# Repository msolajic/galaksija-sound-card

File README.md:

# galaksija-sound-card
"Sound card" for Galaksija computer

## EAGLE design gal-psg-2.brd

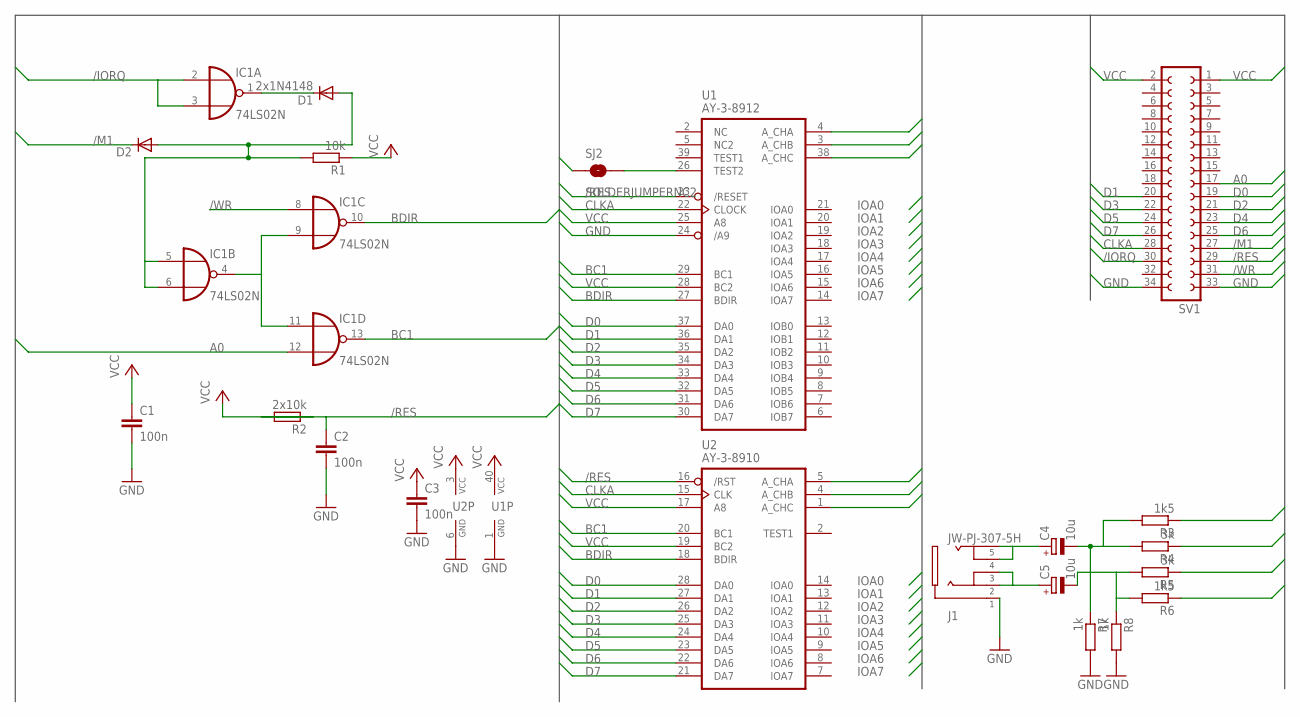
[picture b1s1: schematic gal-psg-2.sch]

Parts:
C1, C2, C3: 100n; C025-024X044
C4, C5: 10u; E1,8-4
D1: 2x1N4148; D-2.5
D2: DIODE-D-2.5; D-2.5
IC1: 74LS02N; DIL14
J1: JW-PJ-307-5H
R1: 10k; 0207/2V
R2: 2x10k; 0207/2V
R3, R6: 1k5; 0207/2V
R4, R5: 3k; 0207/2V
R7, R8: 1k; 0207/2V
SJ2: SOLDERJUMPERNC2; SJ_2S-NOTRACE
SV1: FE17-2W
U1: AY-3-8912; DIL40
U2: AY-3-8910; DIL28-6

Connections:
/IORQ: IC1.2 (I0), IC1.3 (I1), SV1.30
/M1: D2.C, SV1.27
/RES: C2.1, R2.2, SV1.29, U1.23 (/RESET), U2.16 (/RST)
/WR: IC1.8 (I0), SV1.31
A: R3.1, U1.4 (A_CHA), U2.5 (A_CHA)
A0: IC1.12 (I1), SV1.17
B: R4.1, R5.1, U1.3 (A_CHB), U2.4 (A_CHB)
BC1: IC1.13 (O), U1.29 (BC1), U2.20 (BC1)
BDIR: IC1.10 (O), U1.27 (BDIR), U2.18 (BDIR)
C: R6.1, U1.38 (A_CHC), U2.1 (A_CHC)
CLKA: SV1.28, U1.22 (CLOCK), U2.15 (CLK)
D0: SV1.19, U1.37 (DA0), U2.28 (DA0)
D1: SV1.20, U1.36 (DA1), U2.27 (DA1)
D2: SV1.21, U1.35 (DA2), U2.26 (DA2)
D3: SV1.22, U1.34 (DA3), U2.25 (DA3)
D4: SV1.23, U1.33 (DA4), U2.24 (DA4)
D5: SV1.24, U1.32 (DA5), U2.23 (DA5)
D6: SV1.25, U1.31 (DA6), U2.22 (DA6)
D7: SV1.26, U1.30 (DA7), U2.21 (DA7)
GND: C1.2, C2.2, C3.2, IC1.7 (GND), J1.1, R7.2, R8.2, SJ2.1, SV1.33, SV1.34, U1.1 (GND), U1.24 (/A9), U2.6 (GND)
unnamed: SJ2.2, U1.26 (TEST2)
unnamed: D1.C, IC1.1 (O)
unnamed: C5.+, J1.2, J1.3
unnamed: D1.A, D2.A, IC1.5 (I0), IC1.6 (I1), R1.2
unnamed: C4.-, R3.2, R4.2, R7.1
unnamed: IC1.4 (O), IC1.9 (I1), IC1.11 (I0)
unnamed: C4.+, J1.4, J1.5
unnamed: C5.-, R5.2, R6.2, R8.1
VCC: C1.1, C3.1, IC1.14 (VCC), R1.1, R2.1, SV1.1, SV1.2, U1.25 (A8), U1.28 (BC2), U1.40 (VCC), U2.3 (VCC), U2.17 (A8), U2.19 (BC2)

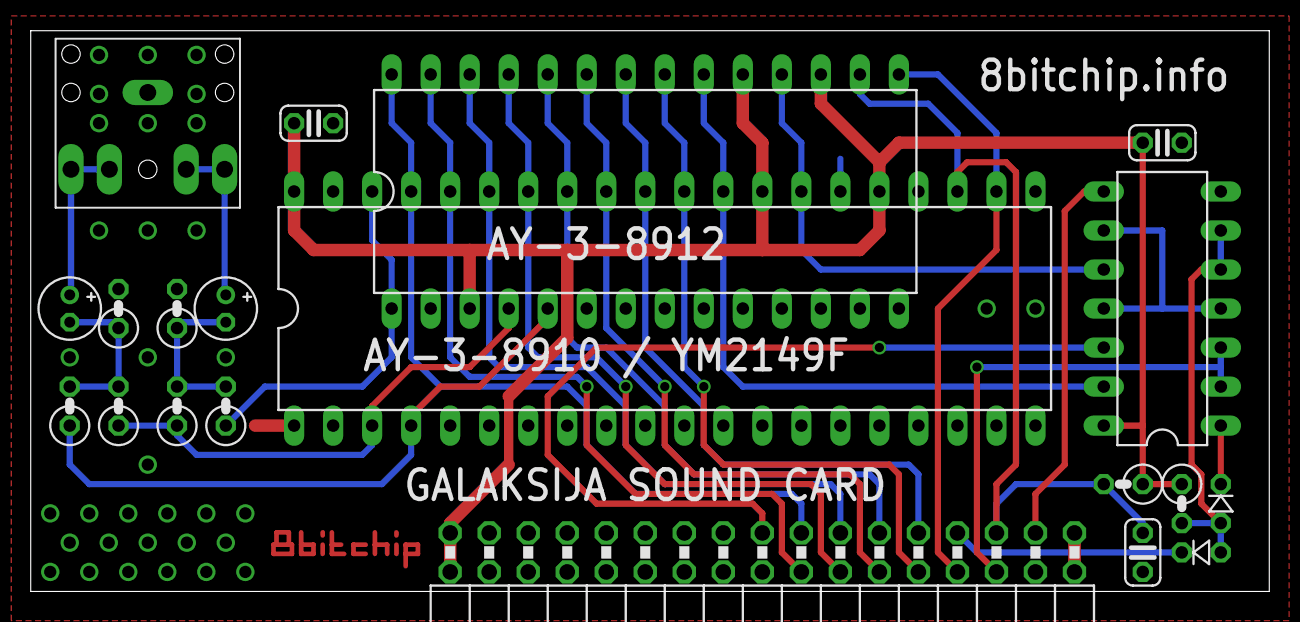
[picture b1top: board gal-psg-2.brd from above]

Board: 2 copper layers, 80.6 x 36.5 mm, 21 parts (1 on the bottom side), 29 nets.

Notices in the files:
parts and their libraries:
SparkFun-Passives: Licensing: Creative Commons ShareAlike 4.0 International - https://creativecommons.org/licenses/by-sa/4.0
